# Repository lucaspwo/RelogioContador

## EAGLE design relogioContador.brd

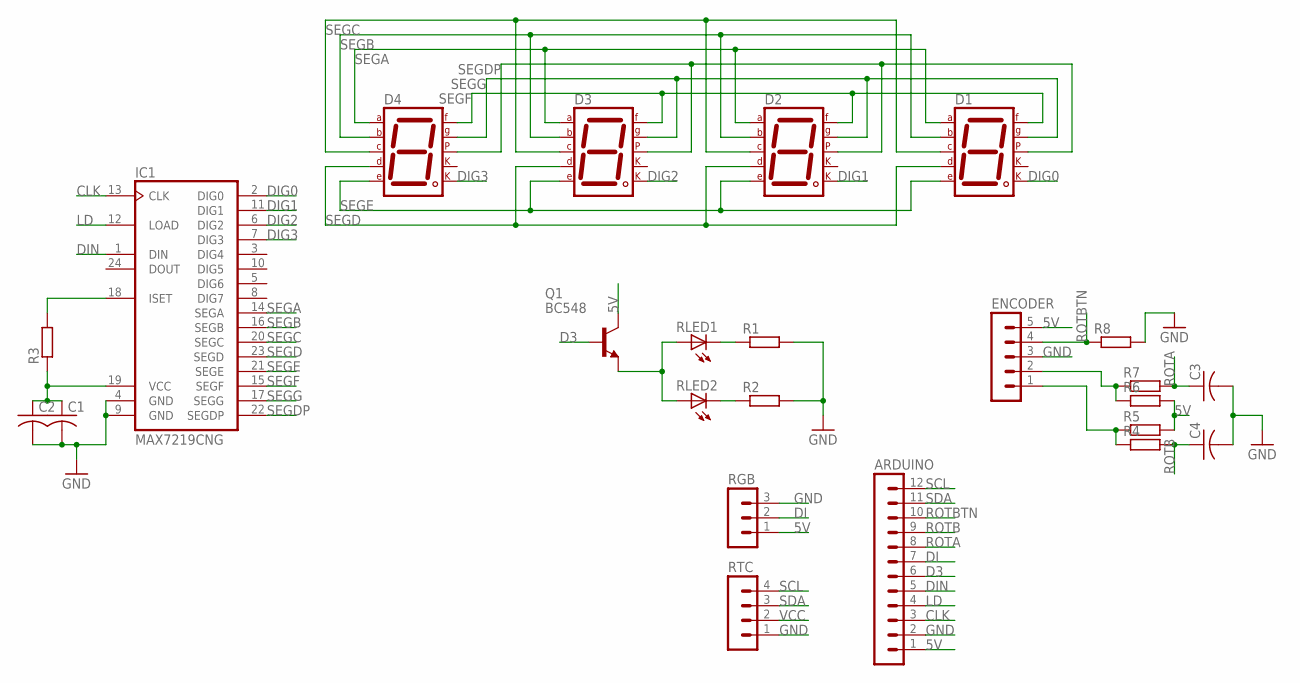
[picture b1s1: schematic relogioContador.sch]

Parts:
ARDUINO: MA12-1
C1, C2, C3, C4: C-US050-025X075; C050-025X075
D1, D2, D3, D4: 7SEG-CK; 7SEG-13
ENCODER: MA05-1
IC1: MAX7219CNG; DIL24-3
Q1: BC548; TO92-EBC
R1, R2, R3, R4, R5, R6, R7, R8: R-EU_0411/15; 0411/15
RGB: MA03-1
RLED1, RLED2: LED3MM
RTC: MA04-1

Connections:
5V: ARDUINO.1, ENCODER.5, Q1.C, R5.2, R6.2, RGB.1
CLK: ARDUINO.3, IC1.13 (CLK)
D3: ARDUINO.6, Q1.B
DI: ARDUINO.7, RGB.2
DIG0: D1.8 (CK2), IC1.2 (DIG0)
DIG1: D2.8 (CK2), IC1.11 (DIG1)
DIG2: D3.8 (CK2), IC1.6 (DIG2)
DIG3: D4.8 (CK2), IC1.7 (DIG3)
DIN: ARDUINO.5, IC1.1 (DIN)
GND: ARDUINO.2, C1.2, C2.2, C3.2, C4.2, ENCODER.3, IC1.4 (GND), IC1.9 (GND), R1.2, R2.2, R8.2, RGB.3, RTC.1
LD: ARDUINO.4, IC1.12 (LOAD)
unnamed: R1.1, RLED1.K (C)
unnamed: R2.1, RLED2.K (C)
unnamed: Q1.E, RLED1.A, RLED2.A
unnamed: ENCODER.2, R6.1, R7.1
unnamed: C1.1, C2.1, IC1.19 (VCC), R3.1
unnamed: IC1.18 (ISET), R3.2
unnamed: ENCODER.1, R4.1, R5.1
ROTA: ARDUINO.8, C3.1, R7.2
ROTB: ARDUINO.9, C4.1, R4.2
ROTBTN: ARDUINO.10, ENCODER.4, R8.1
SCL: ARDUINO.12, RTC.4
SDA: ARDUINO.11, RTC.3
SEGA: D1.7 (A), D2.7 (A), D3.7 (A), D4.7 (A), IC1.14 (SEGA)
SEGB: D1.6 (B), D2.6 (B), D3.6 (B), D4.6 (B), IC1.16 (SEGB)
SEGC: D1.4 (C), D2.4 (C), D3.4 (C), D4.4 (C), IC1.20 (SEGC)
SEGD: D1.2 (D), D2.2 (D), D3.2 (D), D4.2 (D), IC1.23 (SEGD)
SEGDP: D1.5 (DP), D2.5 (DP), D3.5 (DP), D4.5 (DP), IC1.22 (SEGDP)
SEGE: D1.1 (E), D2.1 (E), D3.1 (E), D4.1 (E), IC1.21 (SEGE)
SEGF: D1.9 (F), D2.9 (F), D3.9 (F), D4.9 (F), IC1.15 (SEGF)
SEGG: D1.10 (G), D2.10 (G), D3.10 (G), D4.10 (G), IC1.17 (SEGG)
VCC: RTC.2

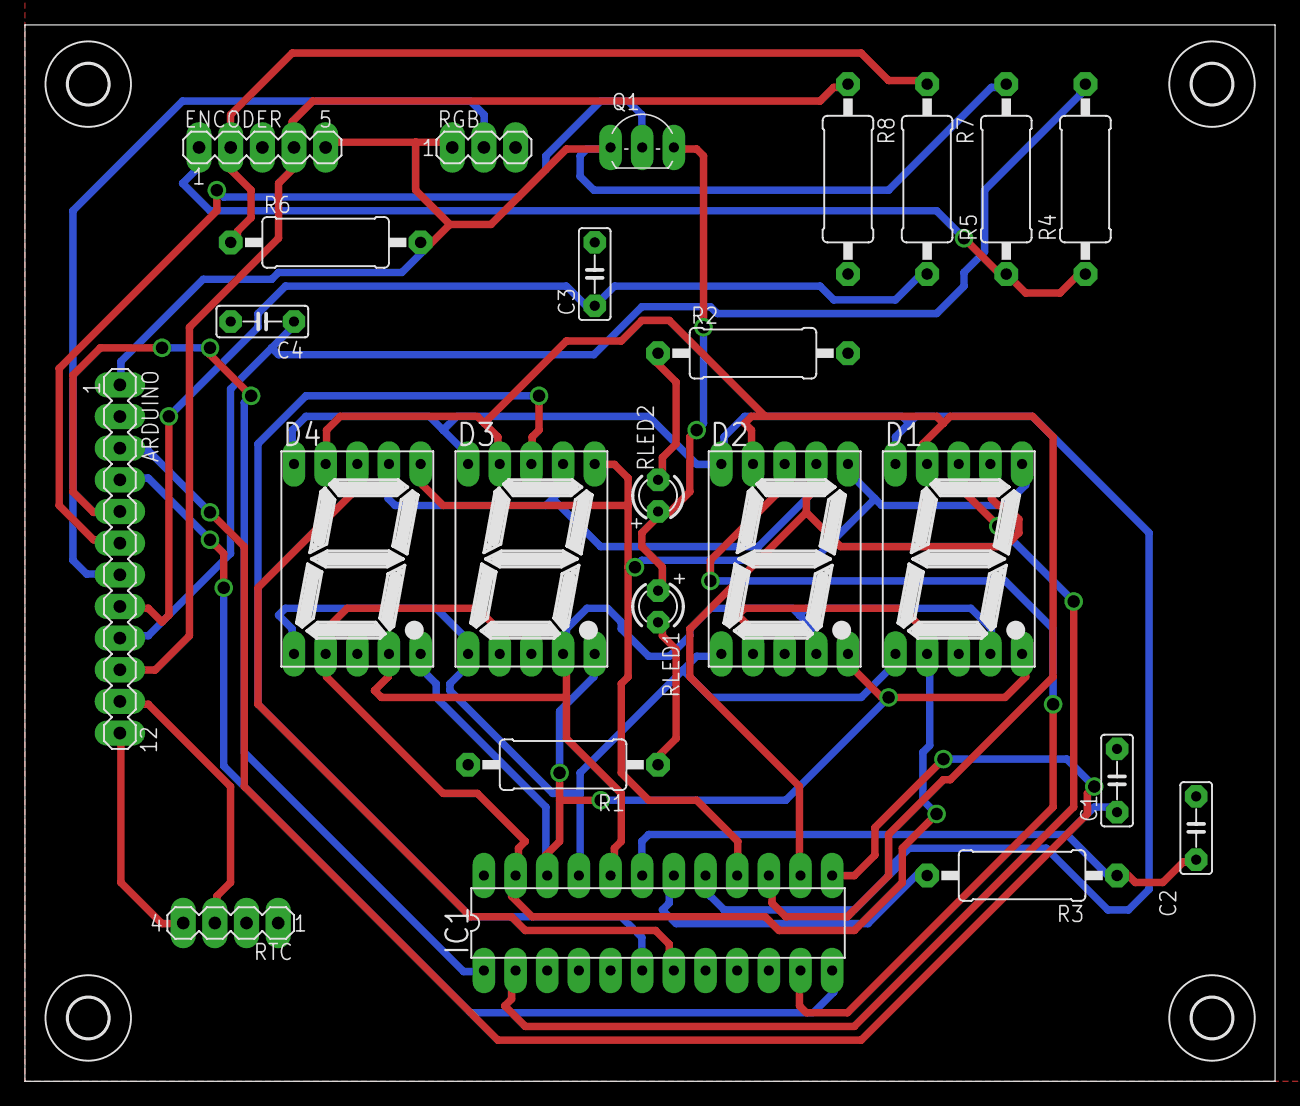
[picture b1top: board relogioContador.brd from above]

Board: 2 copper layers, 100.3 x 84.8 mm, 28 parts (0 on the bottom side), 31 nets.

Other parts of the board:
U$1, U$2, U$3, U$4: 3,2
